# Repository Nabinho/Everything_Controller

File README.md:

# Everything_Controller

Arduino and RF24 based controller to control different types of robots. The codes (controller and receptor example) are available in the "Software" folder, and the electronic project (KiCad project) is available in the "Hardware" folder.

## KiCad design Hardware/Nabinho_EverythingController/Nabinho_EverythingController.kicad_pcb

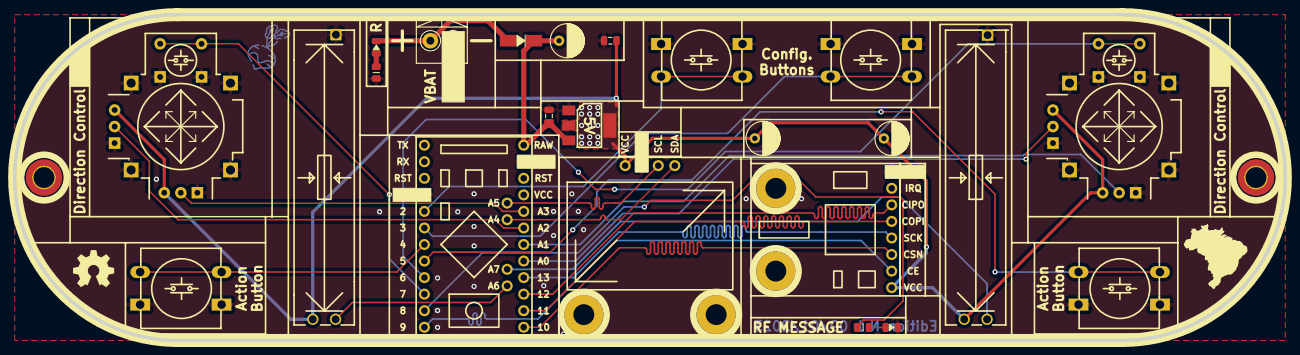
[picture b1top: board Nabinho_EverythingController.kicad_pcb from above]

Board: 2 copper layers, 195.0 x 50.0 mm, 25 parts (0 on the bottom side), 26 nets.

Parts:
C1, C2, C4: 0.1uF; CP_Radial_D5.0mm_P2.50mm
C3, C5: 1uF; C_0805_2012Metric
D1, D3: RED; LED_0805_2012Metric
D2: SS34; D_SMA
Ge: LOGO; opensourceh
J1: NRF24L01; Sparkfun_NRF24L01
J2: 0.96_OLED
J3: Conn_01x02; TerminalBlock_4Ucon_1x02_P3.50mm_Horizontal
R1, R2: 1k; R_0805_2012Metric
RV1, RV2: Slider; Potentiometer_Bourns_PTA3043_Single_Slide
SW1, SW2, SW3, SW4: SW_Push; SW_PUSH-12mm
U1: BB_ProMini; Sparkfun_ProMini
U2: AMS1117-5.0; SOT-223-3_TabPin2
U3, U4: Joystick; XDCR_COM-09032
e: LOGO; brazil

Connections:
+5V: C1.1, C2.1, C5.1, J1.1, J2.1, RV1.1, RV2.1, U2.2 (VO), U3.H1 (H+), U3.V1 (V+), U4.H1 (H+), U4.V1 (V+)
BTN1: SW1.1, U1.5 (2)
BTN2: SW2.1, U1.6 (3)
BTN3: SW3.1, U1.7 (4)
BTN4: SW4.1, U1.8 (5)
CE: J1.2, U1.12 (9)
CIPO: J1.6, U1.19 (12)
COPI: J1.5, U1.18 (11)
CSN: J1.3, U1.17 (10)
GND: C1.2, C2.2, C3.2, C4.2, C5.2, D3.1 (K), J1.8, J2.2, J3.1, R1.1, RV1.3, RV2.3, SW1.2, SW2.2, SW3.2, SW4.2, U1.4 (GND), U1.27 (GND), U2.1 (GND), U3.B2A (SEL-), U3.B2B, U3.H3 (H-), U3.S1 (SHIELD), U3.S2 (SHIELD), U3.S3 (SHIELD), U3.S4 (SHIELD), U3.V3 (V-), U4.B2A (SEL-), U4.B2B, U4.H3 (H-), U4.S1 (SHIELD), U4.S2 (SHIELD), U4.S3 (SHIELD), U4.S4 (SHIELD), U4.V3 (V-)
JOY_X1: U1.21 (A0), U4.V2 (V)
JOY_X2: U1.23 (A2), U3.V2 (V)
JOY_Y1: U1.22 (A1), U4.H2 (H)
JOY_Y2: U1.4 (GND), U3.H2 (H)
J_BTN1: U1.9 (6), U4.B1A (SEL+), U4.B1B
J_BTN2: U1.10 (7), U3.B1A (SEL+), U3.B1B
LED1: R2.1, U1.11 (8)
unnamed: D1.1 (K), D2.2 (A), J3.2
unnamed: D1.2 (A), R1.2
unnamed: D3.2 (A), R2.2
SCK: J1.4, U1.20 (13)
SCL: J2.3, U1.13 (A5)
SDA: J2.4, U1.14 (A4)
SLIDER1: RV2.2, U1.16 (A7)
SLIDER2: RV1.2, U1.15 (A6)
VBUS: C3.1, C4.1, D2.1 (K), U1.28 (VIN), U2.3 (VI)

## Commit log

2023-05-17 CODE OPTIMIZATION
2023-05-20 CODE TRANSLATION
2023-06-14 minor update
2023-06-17 RPi Pico Test
2023-06-18 TX Timeout Update
2023-09-09 ESP32_test
2023-11-08 graphics_update
    Better display graphics to the user.
